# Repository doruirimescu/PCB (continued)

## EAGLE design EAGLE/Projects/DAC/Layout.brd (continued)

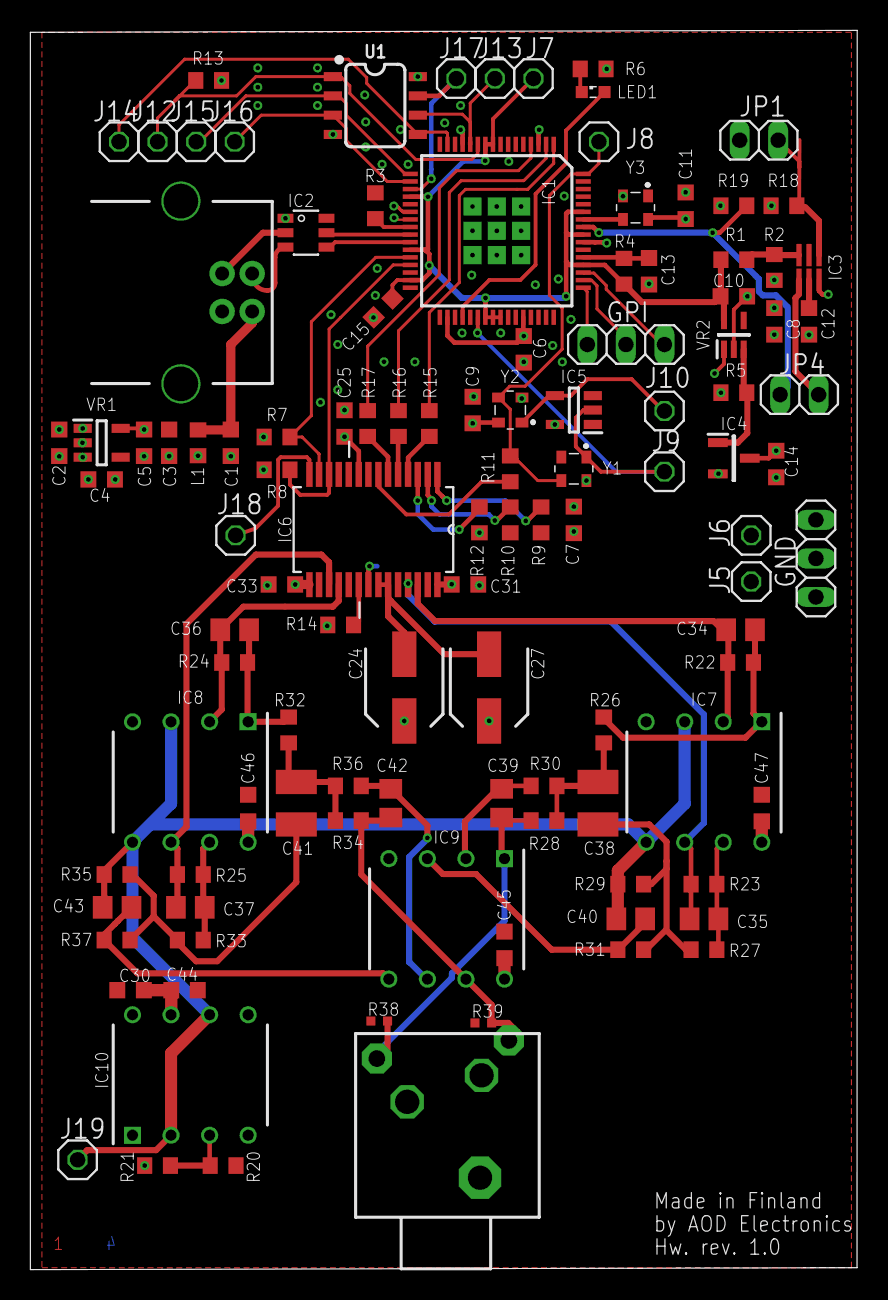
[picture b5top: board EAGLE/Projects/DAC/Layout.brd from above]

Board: 4 copper layers, 54.5 x 81.7 mm, 112 parts (0 on the bottom side), 67 nets.

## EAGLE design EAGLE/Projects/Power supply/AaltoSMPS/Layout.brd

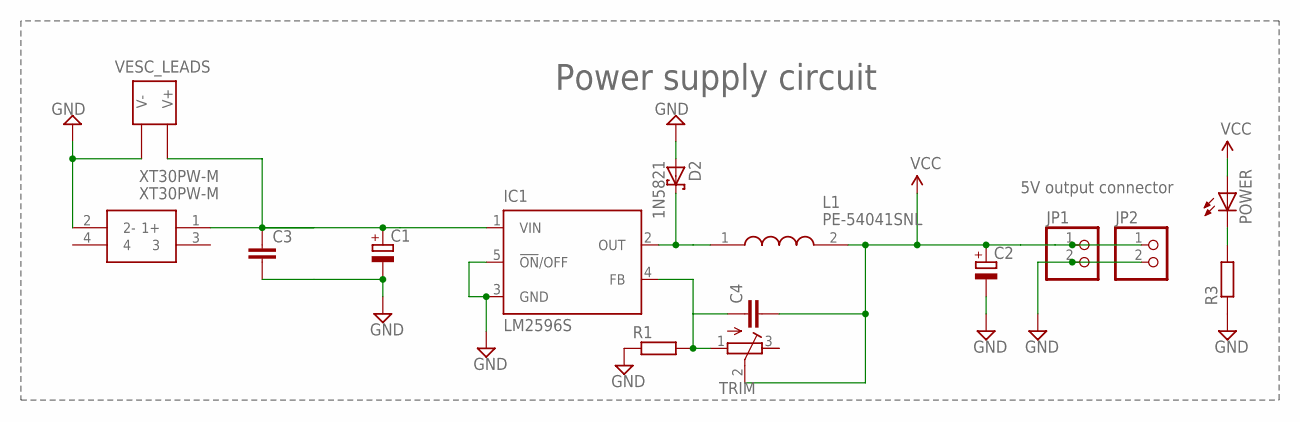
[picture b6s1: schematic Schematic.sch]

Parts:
C1: CPOL-EUE5-13; E5-13
C2: CPOL-EUE2.5-7; E2,5-7
C3: C-EUC1206; C1206
C4: C2,5-3; C2.5-3
D2: 1N5821; DO41-7.6
IC1: LM2596S; TO263-5
JP1, JP2: PINHD-1X2; 1X02
L1: PE-54041SNL; P0846SNLT
POWER: LEDSML0805; SML0805
R1: R-EU_0204/7; 0204/7
R3: R-EU_R1206; R1206
TRIM: R-TRIMM3296W; RTRIM3296W
U$1: VESC_LEADS
XT30PW-M: XT30PW-M; XT30PWM

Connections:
GND: C1.-, C2.-, C3.2, D2.A, IC1.3 (GND), IC1.5 (!ON!/OFF), JP1.2, JP2.2, R1.1, R3.1, U$1.P$2 (V-), XT30PW-M.2 (2-)
IN: C1.+, C3.1, IC1.1 (VIN), U$1.P$1 (V+), XT30PW-M.1 (1+)
unnamed: POWER.C, R3.2
unnamed: D2.C, IC1.2 (OUT), L1.1
unnamed: C4.1, IC1.4 (FB), R1.2, TRIM.1 (A)
VCC: C2.+, C4.2, JP1.1, JP2.1, L1.2, POWER.A, TRIM.2 (S)

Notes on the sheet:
Power supply circuit
5V output connector

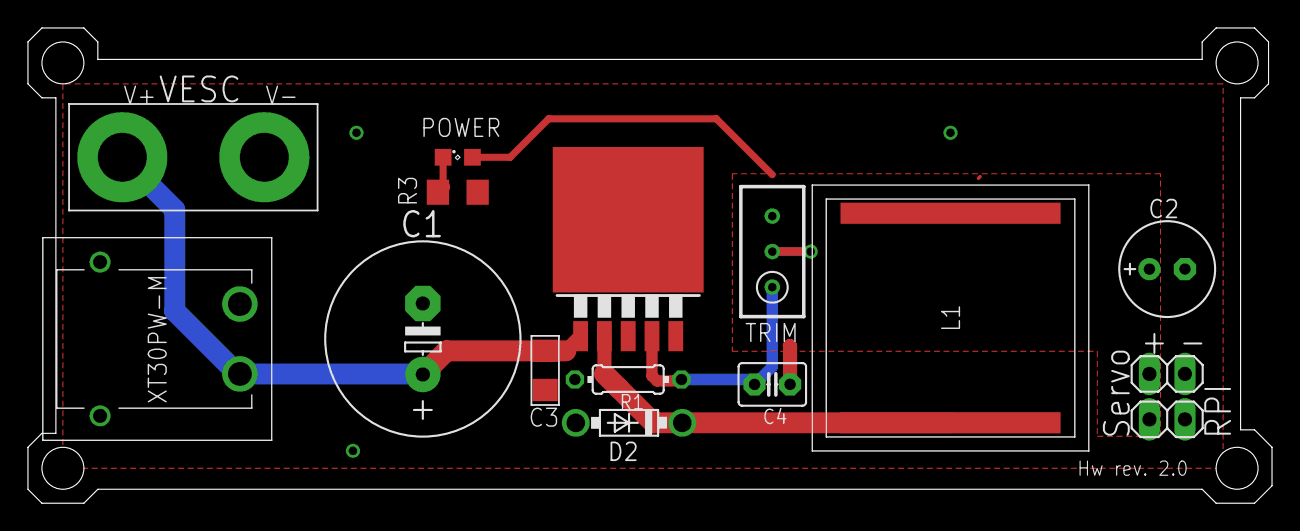
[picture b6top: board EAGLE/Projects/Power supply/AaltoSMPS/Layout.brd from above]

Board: 2 copper layers, 89.0 x 34.0 mm, 15 parts (0 on the bottom side), 6 nets.

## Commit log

2020-10-31 Add initial commit
2021-03-22 Rename accordingly
2021-03-23 Add latest mods
